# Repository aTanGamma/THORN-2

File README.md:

# aTan's THORN-2 RISC-V CPU Project

## What?

This is an implementation of the RISC-V spec using nothing but basic logic and
memory elements. 

The project has been inspired by several similar projects, most
notably [Robert Baruch's LMARV-1](https://www.youtube.com/playlist?list=PLEeZWGE3PwbansoxKjjMKHQqS_2cm8i60),
[James Sharman's JAM-1](https://www.youtube.com/playlist?list=PLFhc0MFC8MiCDOh3cGFji3qQfXziB9yOw)
and [Fabian Schuiki's Superscalar CPU](https://www.youtube.com/playlist?list=PLyR4neQXqQo5nPdEiMbaEJxWiy_UuyNN4).

As of May '26 I'm looking to implement the RV64I spec, with vague plans to 
extend this with the M and maybe F modules. I don't have any timeframe for that
though.

## Why?

IDK. It's fun :)

## That's mental... Where can I see the details?

If you go to `Docs/Writeup/` you can see a proper typewritten rundown on how
everything works and my "design process". There's quite a bit of techy stuff
there, and it's not _guaranteed_ to make sense - it's mostly a document to help
me keep track of what I'm doing between each section.

## Where are the schematics?

See `Schematics/`. This will be spotty for a while yet.

## Can I do anything with this project?

Please do! Though do read the license first. Broadly speaking, keep everything
open-source and don't be evil :)

## What happened to the THORN-1?

¬_¬ it went wrong...

In reality, it was the same as this project, but massively overcomplicated and
everything I learned there helped make this version much simpler. T1 used
pipelined ram for the registers, leading to a 4-phase clock and massive pain in
the ALU, so I abandoned it to start over.

-aTan 2026

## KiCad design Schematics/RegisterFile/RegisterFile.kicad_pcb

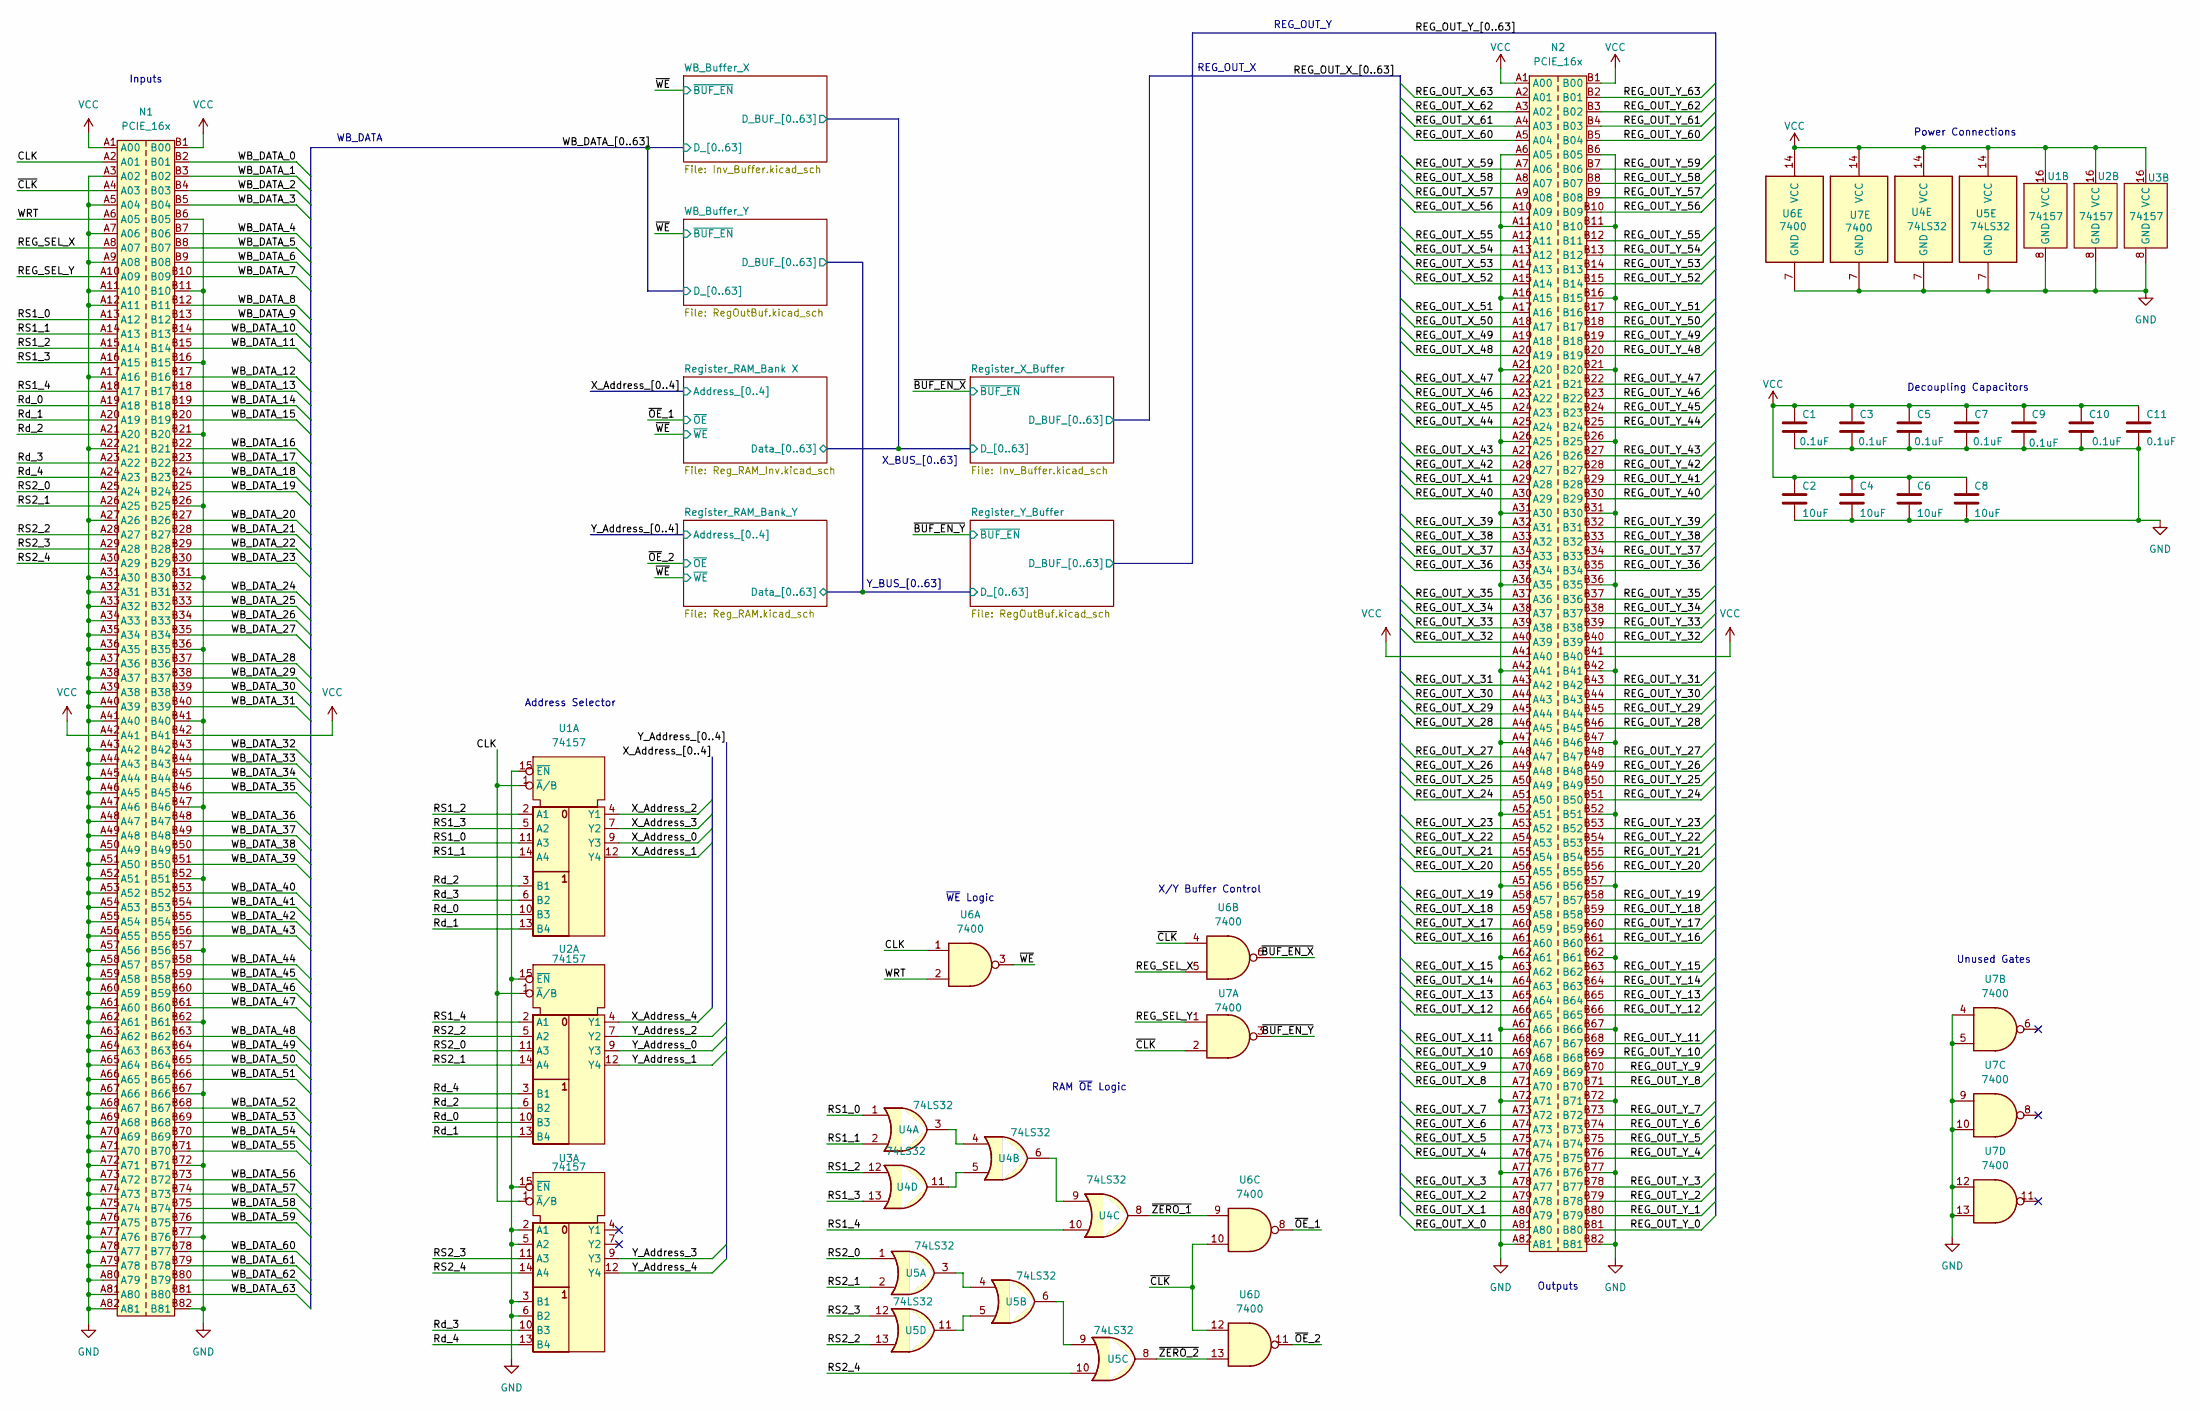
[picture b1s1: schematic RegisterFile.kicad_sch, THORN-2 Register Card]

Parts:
C1, C3, C5, C7, C9, C10, C11: 0.1uF; C_1206_3216Metric
C2, C4, C6, C8: 10uF; C_1206_3216Metric
N1, N2: PCIE_16x; BUS_PCIexpress_x16
U1, U2, U3: 74157; SOIC-16_3.9x9.9mm_P1.27mm
U4, U5: 74LS32; TSSOP-14_4.4x5mm_P0.65mm
U6, U7: 7400; TSSOP-14_4.4x5mm_P0.65mm

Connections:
/CLK: N1.A2 (A01), U1.1 (~A/B), U2.1 (~A/B), U3.1 (~A/B), U6.1
/REG_OUT_X_0: N2.A81 (A80); also elsewhere on the board
/REG_OUT_X_1: N2.A80 (A79); also elsewhere on the board
/REG_OUT_X_2: N2.A79 (A78); also elsewhere on the board
/REG_OUT_X_3: N2.A78 (A77); also elsewhere on the board
/REG_OUT_X_4: N2.A76 (A75); also elsewhere on the board
/REG_OUT_X_5: N2.A75 (A74); also elsewhere on the board
/REG_OUT_X_6: N2.A74 (A73); also elsewhere on the board
/REG_OUT_X_7: N2.A73 (A72); also elsewhere on the board
/REG_OUT_X_8: N2.A71 (A70); also elsewhere on the board
/REG_OUT_X_9: N2.A70 (A69); also elsewhere on the board
/REG_OUT_X_10: N2.A69 (A68); also elsewhere on the board
/REG_OUT_X_11: N2.A68 (A67); also elsewhere on the board
/REG_OUT_X_12: N2.A66 (A65); also elsewhere on the board
/REG_OUT_X_13: N2.A65 (A64); also elsewhere on the board
/REG_OUT_X_14: N2.A64 (A63); also elsewhere on the board
/REG_OUT_X_15: N2.A63 (A62); also elsewhere on the board
/REG_OUT_X_16: N2.A61 (A60); also elsewhere on the board
/REG_OUT_X_17: N2.A60 (A59); also elsewhere on the board
/REG_OUT_X_18: N2.A59 (A58); also elsewhere on the board
/REG_OUT_X_19: N2.A58 (A57); also elsewhere on the board
/REG_OUT_X_20: N2.A56 (A55); also elsewhere on the board
/REG_OUT_X_21: N2.A55 (A54); also elsewhere on the board
/REG_OUT_X_22: N2.A54 (A53); also elsewhere on the board
/REG_OUT_X_23: N2.A53 (A52); also elsewhere on the board
/REG_OUT_X_24: N2.A51 (A50); also elsewhere on the board
/REG_OUT_X_25: N2.A50 (A49); also elsewhere on the board
/REG_OUT_X_26: N2.A49 (A48); also elsewhere on the board
/REG_OUT_X_27: N2.A48 (A47); also elsewhere on the board
/REG_OUT_X_28: N2.A46 (A45); also elsewhere on the board
/REG_OUT_X_29: N2.A45 (A44); also elsewhere on the board
/REG_OUT_X_30: N2.A44 (A43); also elsewhere on the board
/REG_OUT_X_31: N2.A43 (A42); also elsewhere on the board
/REG_OUT_X_32: N2.A40 (A39); also elsewhere on the board
/REG_OUT_X_33: N2.A39 (A38); also elsewhere on the board
/REG_OUT_X_34: N2.A38 (A37); also elsewhere on the board
/REG_OUT_X_35: N2.A37 (A36); also elsewhere on the board
/REG_OUT_X_36: N2.A35 (A34); also elsewhere on the board
/REG_OUT_X_37: N2.A34 (A33); also elsewhere on the board
/REG_OUT_X_38: N2.A33 (A32); also elsewhere on the board
/REG_OUT_X_39: N2.A32 (A31); also elsewhere on the board
/REG_OUT_X_40: N2.A30 (A29); also elsewhere on the board
/REG_OUT_X_41: N2.A29 (A28); also elsewhere on the board
/REG_OUT_X_42: N2.A28 (A27); also elsewhere on the board
/REG_OUT_X_43: N2.A27 (A26); also elsewhere on the board
/REG_OUT_X_44: N2.A25 (A24); also elsewhere on the board
/REG_OUT_X_45: N2.A24 (A23); also elsewhere on the board
/REG_OUT_X_46: N2.A23 (A22); also elsewhere on the board
/REG_OUT_X_47: N2.A22 (A21); also elsewhere on the board
/REG_OUT_X_48: N2.A20 (A19); also elsewhere on the board
/REG_OUT_X_49: N2.A19 (A18); also elsewhere on the board
/REG_OUT_X_50: N2.A18 (A17); also elsewhere on the board
/REG_OUT_X_51: N2.A17 (A16); also elsewhere on the board
/REG_OUT_X_52: N2.A15 (A14); also elsewhere on the board
/REG_OUT_X_53: N2.A14 (A13); also elsewhere on the board
/REG_OUT_X_54: N2.A13 (A12); also elsewhere on the board
/REG_OUT_X_55: N2.A12 (A11); also elsewhere on the board
/REG_OUT_X_56: N2.A10 (A09); also elsewhere on the board
/REG_OUT_X_57: N2.A9 (A08); also elsewhere on the board
/REG_OUT_X_58: N2.A8 (A07); also elsewhere on the board
/REG_OUT_X_59: N2.A7 (A06); also elsewhere on the board
/REG_OUT_X_60: N2.A5 (A04); also elsewhere on the board
/REG_OUT_X_61: N2.A4 (A03); also elsewhere on the board
/REG_OUT_X_62: N2.A3 (A02); also elsewhere on the board
/REG_OUT_X_63: N2.A2 (A01); also elsewhere on the board
/REG_OUT_Y_0: N2.B81 (B80); also elsewhere on the board
/REG_OUT_Y_1: N2.B80 (B79); also elsewhere on the board
/REG_OUT_Y_2: N2.B79 (B78); also elsewhere on the board
/REG_OUT_Y_3: N2.B78 (B77); also elsewhere on the board
/REG_OUT_Y_4: N2.B76 (B75); also elsewhere on the board
/REG_OUT_Y_5: N2.B75 (B74); also elsewhere on the board
/REG_OUT_Y_6: N2.B74 (B73); also elsewhere on the board
/REG_OUT_Y_7: N2.B73 (B72); also elsewhere on the board
/REG_OUT_Y_8: N2.B71 (B70); also elsewhere on the board
/REG_OUT_Y_9: N2.B70 (B69); also elsewhere on the board
/REG_OUT_Y_10: N2.B69 (B68); also elsewhere on the board
/REG_OUT_Y_11: N2.B68 (B67); also elsewhere on the board
/REG_OUT_Y_12: N2.B66 (B65); also elsewhere on the board
/REG_OUT_Y_13: N2.B65 (B64); also elsewhere on the board
/REG_OUT_Y_14: N2.B64 (B63); also elsewhere on the board
/REG_OUT_Y_15: N2.B63 (B62); also elsewhere on the board
/REG_OUT_Y_16: N2.B61 (B60); also elsewhere on the board
/REG_OUT_Y_17: N2.B60 (B59); also elsewhere on the board
/REG_OUT_Y_18: N2.B59 (B58); also elsewhere on the board
/REG_OUT_Y_19: N2.B58 (B57); also elsewhere on the board
/REG_OUT_Y_20: N2.B56 (B55); also elsewhere on the board
/REG_OUT_Y_21: N2.B55 (B54); also elsewhere on the board
/REG_OUT_Y_22: N2.B54 (B53); also elsewhere on the board
/REG_OUT_Y_23: N2.B53 (B52); also elsewhere on the board
/REG_OUT_Y_24: N2.B51 (B50); also elsewhere on the board
/REG_OUT_Y_25: N2.B50 (B49); also elsewhere on the board
/REG_OUT_Y_26: N2.B49 (B48); also elsewhere on the board
/REG_OUT_Y_27: N2.B48 (B47); also elsewhere on the board
/REG_OUT_Y_28: N2.B46 (B45); also elsewhere on the board
/REG_OUT_Y_29: N2.B45 (B44); also elsewhere on the board
/REG_OUT_Y_30: N2.B44 (B43); also elsewhere on the board
/REG_OUT_Y_31: N2.B43 (B42); also elsewhere on the board
/REG_OUT_Y_32: N2.B40 (B39); also elsewhere on the board
/REG_OUT_Y_33: N2.B39 (B38); also elsewhere on the board
/REG_OUT_Y_34: N2.B38 (B37); also elsewhere on the board
/REG_OUT_Y_35: N2.B37 (B36); also elsewhere on the board
/REG_OUT_Y_36: N2.B35 (B34); also elsewhere on the board
/REG_OUT_Y_37: N2.B34 (B33); also elsewhere on the board
/REG_OUT_Y_38: N2.B33 (B32); also elsewhere on the board
/REG_OUT_Y_39: N2.B32 (B31); also elsewhere on the board
/REG_OUT_Y_40: N2.B30 (B29); also elsewhere on the board
/REG_OUT_Y_41: N2.B29 (B28); also elsewhere on the board
/REG_OUT_Y_42: N2.B28 (B27); also elsewhere on the board
/REG_OUT_Y_43: N2.B27 (B26); also elsewhere on the board
/REG_OUT_Y_44: N2.B25 (B24); also elsewhere on the board
/REG_OUT_Y_45: N2.B24 (B23); also elsewhere on the board
/REG_OUT_Y_46: N2.B23 (B22); also elsewhere on the board
/REG_OUT_Y_47: N2.B22 (B21); also elsewhere on the board
/REG_OUT_Y_48: N2.B20 (B19); also elsewhere on the board
/REG_OUT_Y_49: N2.B19 (B18); also elsewhere on the board
/REG_OUT_Y_50: N2.B18 (B17); also elsewhere on the board
/REG_OUT_Y_51: N2.B17 (B16); also elsewhere on the board
/REG_OUT_Y_52: N2.B15 (B14); also elsewhere on the board
/REG_OUT_Y_53: N2.B14 (B13); also elsewhere on the board
/REG_OUT_Y_54: N2.B13 (B12); also elsewhere on the board
/REG_OUT_Y_55: N2.B12 (B11); also elsewhere on the board
/REG_OUT_Y_56: N2.B10 (B09); also elsewhere on the board
/REG_OUT_Y_57: N2.B9 (B08); also elsewhere on the board
/REG_OUT_Y_58: N2.B8 (B07); also elsewhere on the board
/REG_OUT_Y_59: N2.B7 (B06); also elsewhere on the board
/REG_OUT_Y_60: N2.B5 (B04); also elsewhere on the board
/REG_OUT_Y_61: N2.B4 (B03); also elsewhere on the board
/REG_OUT_Y_62: N2.B3 (B02); also elsewhere on the board
/REG_OUT_Y_63: N2.B2 (B01); also elsewhere on the board
/REG_SEL_X: N1.A8 (A07), U6.5
/REG_SEL_Y: N1.A10 (A09), U7.1
/RS1_0: N1.A13 (A12), U1.11 (A3), U4.1
/RS1_1: N1.A14 (A13), U1.14 (A4), U4.2
/RS1_2: N1.A15 (A14), U1.2 (A1), U4.12
/RS1_3: N1.A16 (A15), U1.5 (A2), U4.13
/RS1_4: N1.A18 (A17), U2.2 (A1), U4.10
/RS2_0: N1.A25 (A24), U2.11 (A3), U5.1
/RS2_1: N1.A26 (A25), U2.14 (A4), U5.2
/RS2_2: N1.A28 (A27), U2.5 (A2), U5.13
/RS2_3: N1.A29 (A28), U3.11 (A3), U5.12
/RS2_4: N1.A30 (A29), U3.14 (A4), U5.10
/Rd_0: N1.A19 (A18), U1.10 (B3), U2.10 (B3)
/Rd_1: N1.A20 (A19), U1.13 (B4), U2.13 (B4)
/Rd_2: N1.A21 (A20), U1.3 (B1), U2.6 (B2)
/Rd_3: N1.A23 (A22), U1.6 (B2), U3.10 (B3)
/Rd_4: N1.A24 (A23), U2.3 (B1), U3.13 (B4)
/WB_DATA_0: N1.B2 (B01); also elsewhere on the board
/WB_DATA_1: N1.B3 (B02); also elsewhere on the board
/WB_DATA_2: N1.B4 (B03); also elsewhere on the board
/WB_DATA_3: N1.B5 (B04); also elsewhere on the board
/WB_DATA_4: N1.B7 (B06); also elsewhere on the board
/WB_DATA_5: N1.B8 (B07); also elsewhere on the board
/WB_DATA_6: N1.B9 (B08); also elsewhere on the board
/WB_DATA_7: N1.B10 (B09); also elsewhere on the board
/WB_DATA_8: N1.B12 (B11); also elsewhere on the board
/WB_DATA_9: N1.B13 (B12); also elsewhere on the board
/WB_DATA_10: N1.B14 (B13); also elsewhere on the board
/WB_DATA_11: N1.B15 (B14); also elsewhere on the board
/WB_DATA_12: N1.B17 (B16); also elsewhere on the board
/WB_DATA_13: N1.B18 (B17); also elsewhere on the board
/WB_DATA_14: N1.B19 (B18); also elsewhere on the board
/WB_DATA_15: N1.B20 (B19); also elsewhere on the board
/WB_DATA_16: N1.B22 (B21); also elsewhere on the board
/WB_DATA_17: N1.B23 (B22); also elsewhere on the board
/WB_DATA_18: N1.B24 (B23); also elsewhere on the board
/WB_DATA_19: N1.B25 (B24); also elsewhere on the board
/WB_DATA_20: N1.B27 (B26); also elsewhere on the board
/WB_DATA_21: N1.B28 (B27); also elsewhere on the board
/WB_DATA_22: N1.B29 (B28); also elsewhere on the board
/WB_DATA_23: N1.B30 (B29); also elsewhere on the board
/WB_DATA_24: N1.B32 (B31); also elsewhere on the board
/WB_DATA_25: N1.B33 (B32); also elsewhere on the board
/WB_DATA_26: N1.B34 (B33); also elsewhere on the board
/WB_DATA_27: N1.B35 (B34); also elsewhere on the board
/WB_DATA_28: N1.B37 (B36); also elsewhere on the board
/WB_DATA_29: N1.B38 (B37); also elsewhere on the board
/WB_DATA_30: N1.B39 (B38); also elsewhere on the board
/WB_DATA_31: N1.B40 (B39); also elsewhere on the board
/WB_DATA_32: N1.B43 (B42); also elsewhere on the board
/WB_DATA_33: N1.B44 (B43); also elsewhere on the board
/WB_DATA_34: N1.B45 (B44); also elsewhere on the board
/WB_DATA_35: N1.B46 (B45); also elsewhere on the board
/WB_DATA_36: N1.B48 (B47); also elsewhere on the board
/WB_DATA_37: N1.B49 (B48); also elsewhere on the board
/WB_DATA_38: N1.B50 (B49); also elsewhere on the board
/WB_DATA_39: N1.B51 (B50); also elsewhere on the board
/WB_DATA_40: N1.B53 (B52); also elsewhere on the board
/WB_DATA_41: N1.B54 (B53); also elsewhere on the board
/WB_DATA_42: N1.B55 (B54); also elsewhere on the board
/WB_DATA_43: N1.B56 (B55); also elsewhere on the board
/WB_DATA_44: N1.B58 (B57); also elsewhere on the board
/WB_DATA_45: N1.B59 (B58); also elsewhere on the board
/WB_DATA_46: N1.B60 (B59); also elsewhere on the board
/WB_DATA_47: N1.B61 (B60); also elsewhere on the board
/WB_DATA_48: N1.B63 (B62); also elsewhere on the board
/WB_DATA_49: N1.B64 (B63); also elsewhere on the board
/WB_DATA_50: N1.B65 (B64); also elsewhere on the board
/WB_DATA_51: N1.B66 (B65); also elsewhere on the board
/WB_DATA_52: N1.B68 (B67); also elsewhere on the board
/WB_DATA_53: N1.B69 (B68); also elsewhere on the board
/WB_DATA_54: N1.B70 (B69); also elsewhere on the board
/WB_DATA_55: N1.B71 (B70); also elsewhere on the board
/WB_DATA_56: N1.B73 (B72); also elsewhere on the board
/WB_DATA_57: N1.B74 (B73); also elsewhere on the board
/WB_DATA_58: N1.B75 (B74); also elsewhere on the board
/WB_DATA_59: N1.B76 (B75); also elsewhere on the board
/WB_DATA_60: N1.B78 (B77); also elsewhere on the board
/WB_DATA_61: N1.B79 (B78); also elsewhere on the board
/WB_DATA_62: N1.B80 (B79); also elsewhere on the board
/WB_DATA_63: N1.B81 (B80); also elsewhere on the board
/WRT: N1.A6 (A05), U6.2
/X_Address_0: U1.9 (Y3); also elsewhere on the board
/X_Address_1: U1.12 (Y4); also elsewhere on the board
/X_Address_2: U1.4 (Y1); also elsewhere on the board
/X_Address_3: U1.7 (Y2); also elsewhere on the board
/X_Address_4: U2.4 (Y1); also elsewhere on the board
/Y_Address_0: U2.9 (Y3); also elsewhere on the board
/Y_Address_1: U2.12 (Y4); also elsewhere on the board
/Y_Address_2: U2.7 (Y2); also elsewhere on the board
/Y_Address_3: U3.9 (Y3); also elsewhere on the board
/Y_Address_4: U3.12 (Y4); also elsewhere on the board
/~BUF_EN_X: U6.6; also elsewhere on the board
/~BUF_EN_Y: U7.3; also elsewhere on the board
/~CLK: N1.A4 (A03), U6.4, U6.10, U6.12, U7.2
/~OE_1: U6.8; also elsewhere on the board
/~OE_2: U6.11; also elsewhere on the board
/~WE: U6.3; also elsewhere on the board
/~ZERO_1: U4.8, U6.9
/~ZERO_2: U5.8, U6.13
GND: C1.2, C2.2, C3.2, C4.2, C5.2, C6.2, C7.2, C8.2, C9.2, C10.2, C11.2, N1.A3 (A02), N1.A5 (A04), N1.A7 (A06), N1.A9 (A08), N1.A11 (A10), N1.A12 (A11), N1.A17 (A16), N1.A22 (A21), N1.A27 (A26), N1.A31 (A30), N1.A32 (A31), N1.A33 (A32), N1.A34 (A33), N1.A35 (A34), N1.A36 (A35), N1.A37 (A36), N1.A38 (A37), N1.A39 (A38), N1.A40 (A39), N1.A41 (A40), N1.A43 (A42), N1.A44 (A43), N1.A45 (A44), N1.A46 (A45), N1.A47 (A46), N1.A48 (A47), N1.A49 (A48), N1.A50 (A49), N1.A51 (A50), N1.A52 (A51), N1.A53 (A52), N1.A54 (A53), N1.A55 (A54), N1.A56 (A55), N1.A57 (A56), N1.A58 (A57), N1.A59 (A58), N1.A60 (A59), N1.A61 (A60), N1.A62 (A61), N1.A63 (A62), N1.A64 (A63), N1.A65 (A64), N1.A66 (A65), N1.A67 (A66), N1.A68 (A67), N1.A69 (A68), N1.A70 (A69), N1.A71 (A70), N1.A72 (A71), N1.A73 (A72), N1.A74 (A73), N1.A75 (A74), N1.A76 (A75), N1.A77 (A76), N1.A78 (A77), N1.A79 (A78), N1.A80 (A79), N1.A81 (A80), N1.A82 (A81), N1.B6 (B05), N1.B11 (B10), N1.B16 (B15), N1.B21 (B20), N1.B26 (B25), N1.B31 (B30), N1.B36 (B35), N1.B41 (B40), N1.B47 (B46), N1.B52 (B51), N1.B57 (B56), N1.B62 (B61), N1.B67 (B66), N1.B72 (B71), N1.B77 (B76), N1.B82 (B81), N2.A6 (A05), N2.A11 (A10), N2.A16 (A15), N2.A21 (A20), N2.A26 (A25), N2.A31 (A30), N2.A36 (A35), N2.A42 (A41), N2.A47 (A46), N2.A52 (A51), N2.A57 (A56), N2.A62 (A61), N2.A67 (A66), N2.A72 (A71), N2.A77 (A76), N2.A82 (A81), N2.B6 (B05), N2.B11 (B10), N2.B16 (B15), N2.B21 (B20), N2.B26 (B25), N2.B31 (B30), N2.B36 (B35), N2.B42 (B41), N2.B47 (B46), N2.B52 (B51), N2.B57 (B56), N2.B62 (B61), N2.B67 (B66), N2.B72 (B71), N2.B77 (B76), N2.B82 (B81), U1.8 (GND), U1.15 (~EN), U2.8 (GND), U2.15 (~EN), U3.2 (A1), U3.3 (B1), U3.5 (A2), U3.6 (B2), U3.8 (GND), U3.15 (~EN), U4.7 (GND), U5.7 (GND), U6.7 (GND), U7.4, U7.5, U7.7 (GND), U7.9, U7.10, U7.12, U7.13; also elsewhere on the board
unnamed: U4.3, U4.4
unnamed: U4.6, U4.9
unnamed: U4.5, U4.11
unnamed: U5.3, U5.4
unnamed: U5.6, U5.9
unnamed: U5.5, U5.11
VCC: C1.1, C2.1, C3.1, C4.1, C5.1, C6.1, C7.1, C8.1, C9.1, C10.1, C11.1, N1.A1 (A00), N1.A42 (A41), N1.B1 (B00), N1.B42 (B41), N2.A1 (A00), N2.A41 (A40), N2.B1 (B00), N2.B41 (B40), U1.16 (VCC), U2.16 (VCC), U3.16 (VCC), U4.14 (VCC), U5.14 (VCC), U6.14 (VCC), U7.14 (VCC); also elsewhere on the board

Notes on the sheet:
RAM ~{OE} Logic
Power Connections
Y_BUS_[0..63]
X_BUS_[0..63]
Unused Gates
Decoupling Capacitors
REG_OUT_X
REG_OUT_Y
~{WE} Logic
Outputs
WB_DATA
Address Selector
Inputs
X/Y Buffer Control

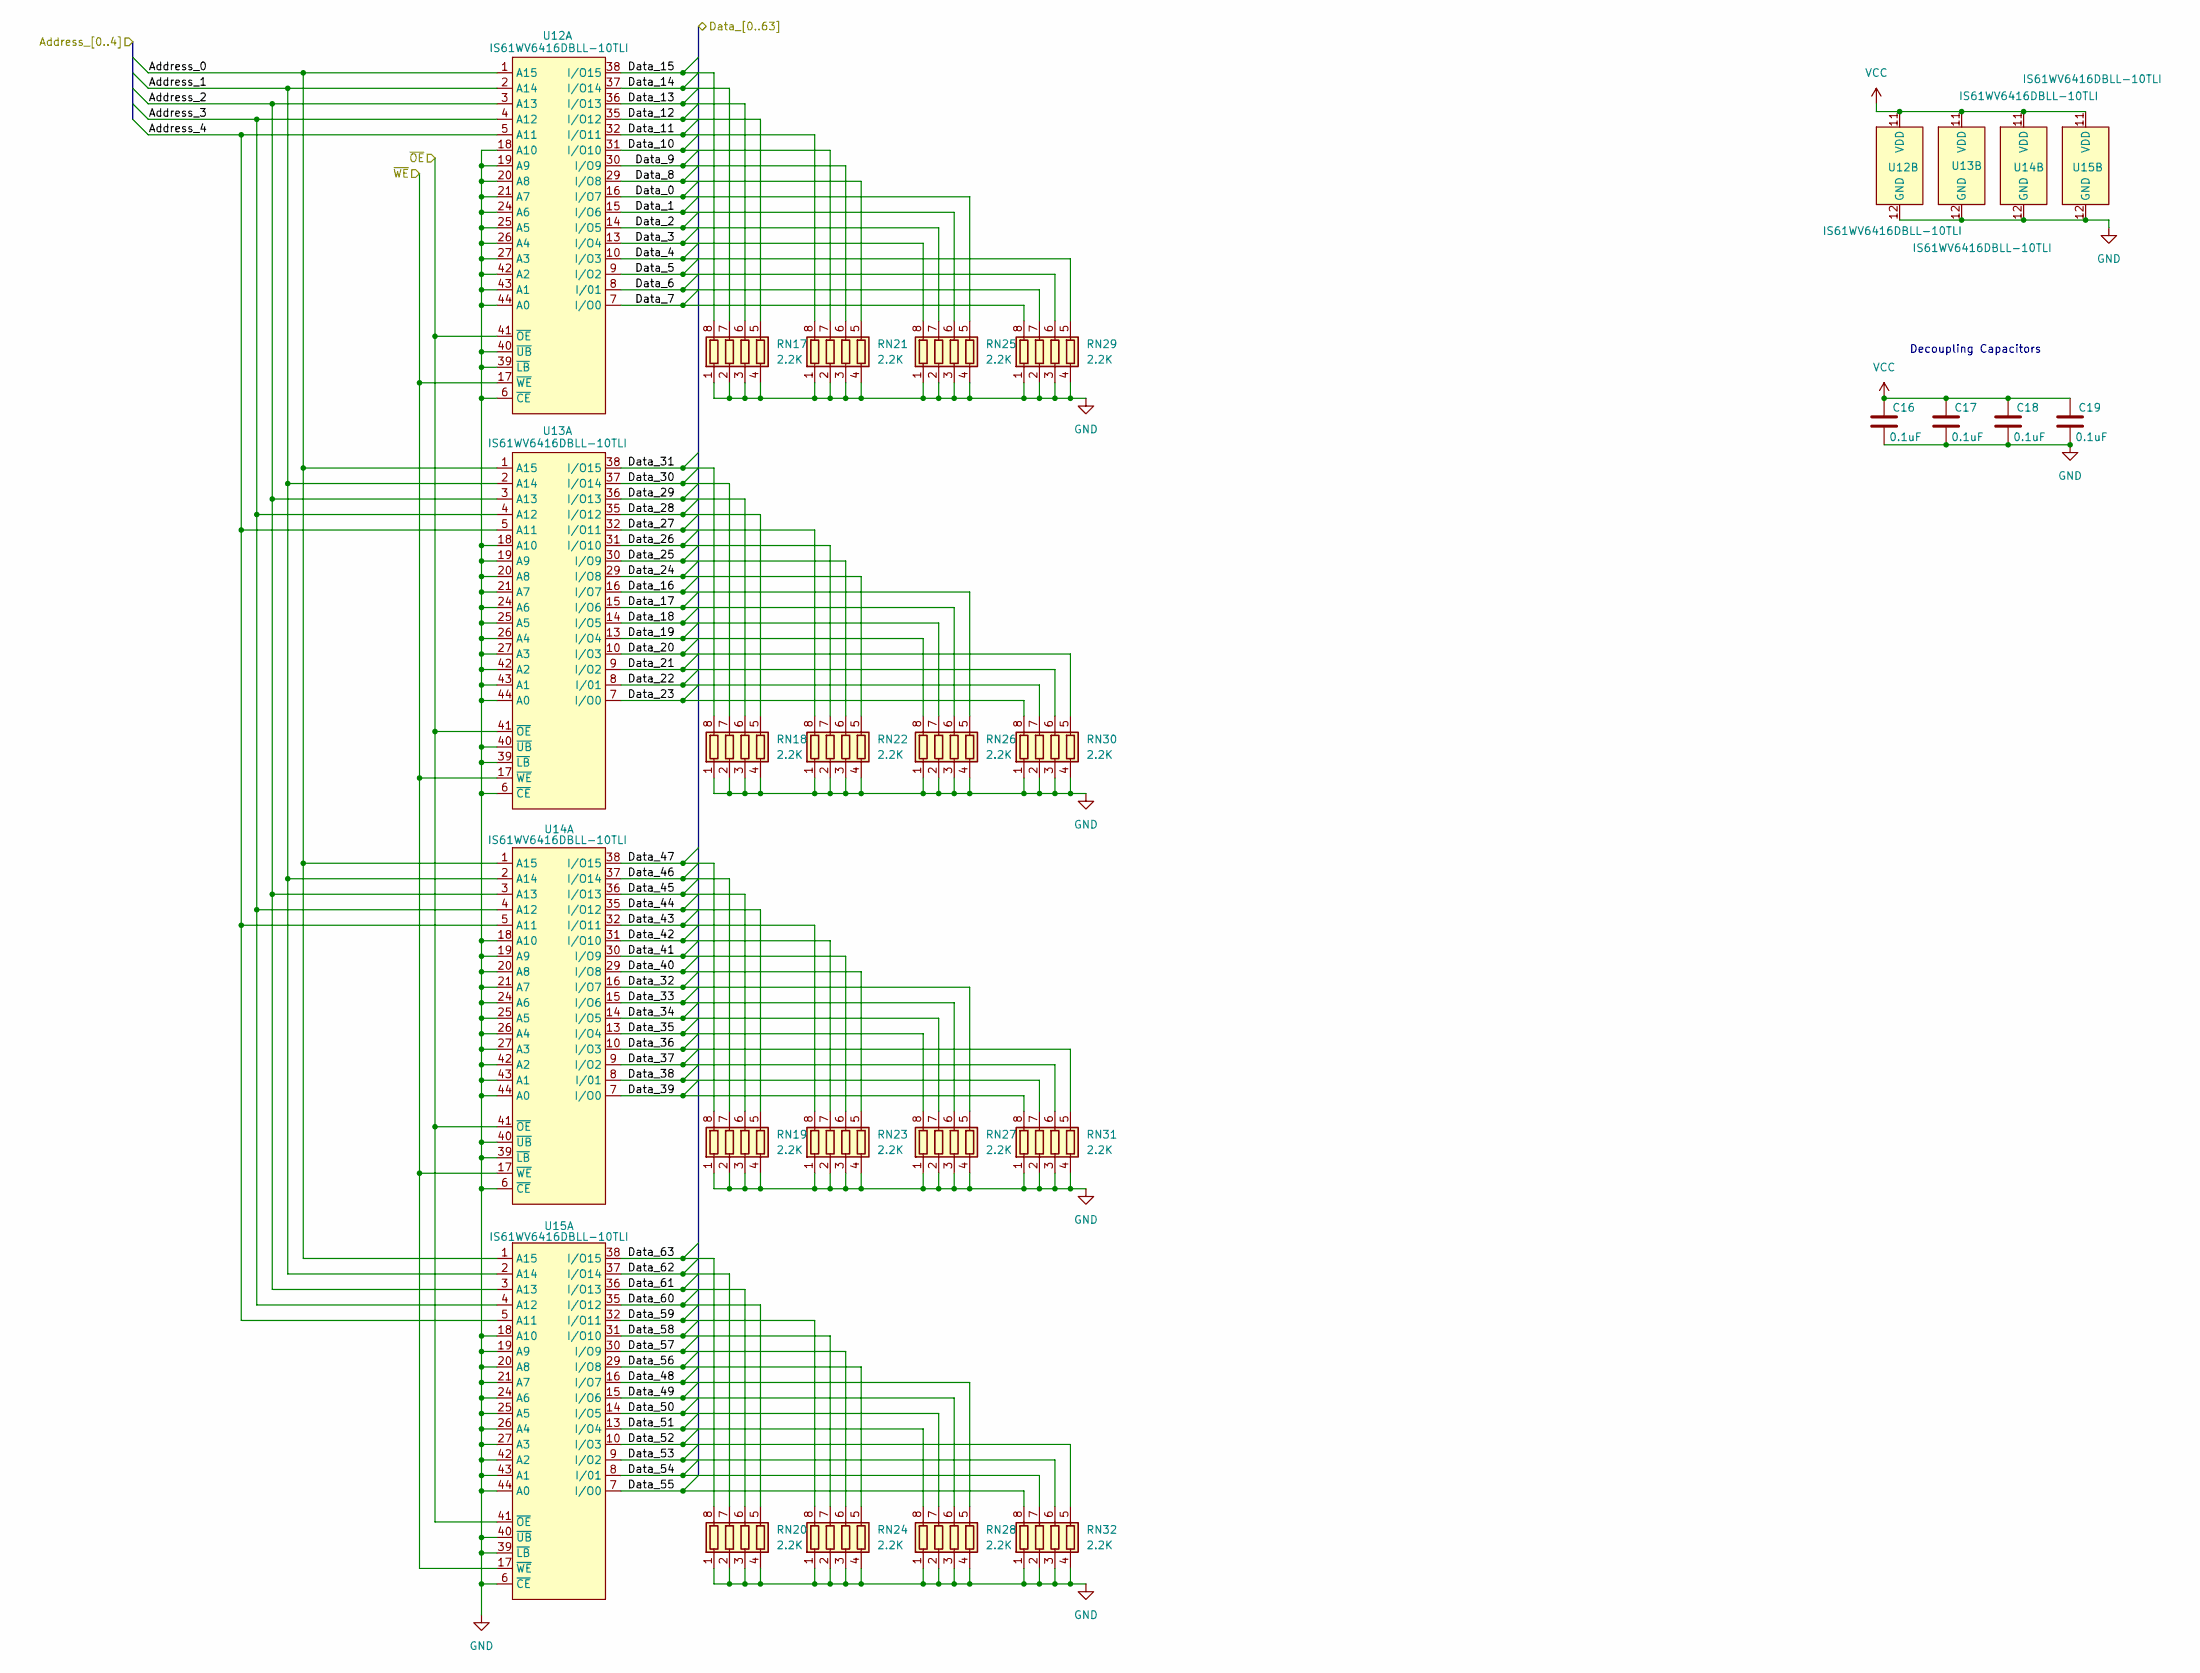
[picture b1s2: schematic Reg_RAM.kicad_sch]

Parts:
C16, C17, C18, C19: 0.1uF; C_1206_3216Metric
RN17, RN18, RN19, RN20, RN21, RN22, RN23, RN24, RN25, RN26, RN27, RN28, RN29, RN30, RN31, RN32: 2.2K; R_Array_Convex_4x0603
U12, U13, U14, U15: IS61WV6416DBLL-10TLI; TSOP-II-44_10.16x18.41mm_P0.8mm

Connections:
/Register_RAM_Bank_Y/Data_0: RN25.5 (R4.2), U12.16 (I/O7); also elsewhere on the board
/Register_RAM_Bank_Y/Data_1: RN25.6 (R3.2), U12.15 (I/O6); also elsewhere on the board
/Register_RAM_Bank_Y/Data_2: RN25.7 (R2.2), U12.14 (I/O5); also elsewhere on the board
/Register_RAM_Bank_Y/Data_3: RN25.8 (R1.2), U12.13 (I/O4); also elsewhere on the board
/Register_RAM_Bank_Y/Data_4: RN29.5 (R4.2), U12.10 (I/O3); also elsewhere on the board
/Register_RAM_Bank_Y/Data_5: RN29.6 (R3.2), U12.9 (I/O2); also elsewhere on the board
/Register_RAM_Bank_Y/Data_6: RN29.7 (R2.2), U12.8 (I/01); also elsewhere on the board
/Register_RAM_Bank_Y/Data_7: RN29.8 (R1.2), U12.7 (I/O0); also elsewhere on the board
/Register_RAM_Bank_Y/Data_8: RN21.5 (R4.2), U12.29 (I/O8); also elsewhere on the board
/Register_RAM_Bank_Y/Data_9: RN21.6 (R3.2), U12.30 (I/O9); also elsewhere on the board
/Register_RAM_Bank_Y/Data_10: RN21.7 (R2.2), U12.31 (I/O10); also elsewhere on the board
/Register_RAM_Bank_Y/Data_11: RN21.8 (R1.2), U12.32 (I/O11); also elsewhere on the board
/Register_RAM_Bank_Y/Data_12: RN17.5 (R4.2), U12.35 (I/O12); also elsewhere on the board
/Register_RAM_Bank_Y/Data_13: RN17.6 (R3.2), U12.36 (I/O13); also elsewhere on the board
/Register_RAM_Bank_Y/Data_14: RN17.7 (R2.2), U12.37 (I/O14); also elsewhere on the board
/Register_RAM_Bank_Y/Data_15: RN17.8 (R1.2), U12.38 (I/O15); also elsewhere on the board
/Register_RAM_Bank_Y/Data_16: RN26.5 (R4.2), U13.16 (I/O7); also elsewhere on the board
/Register_RAM_Bank_Y/Data_17: RN26.6 (R3.2), U13.15 (I/O6); also elsewhere on the board
/Register_RAM_Bank_Y/Data_18: RN26.7 (R2.2), U13.14 (I/O5); also elsewhere on the board
/Register_RAM_Bank_Y/Data_19: RN26.8 (R1.2), U13.13 (I/O4); also elsewhere on the board
/Register_RAM_Bank_Y/Data_20: RN30.5 (R4.2), U13.10 (I/O3); also elsewhere on the board
/Register_RAM_Bank_Y/Data_21: RN30.6 (R3.2), U13.9 (I/O2); also elsewhere on the board
/Register_RAM_Bank_Y/Data_22: RN30.7 (R2.2), U13.8 (I/01); also elsewhere on the board
/Register_RAM_Bank_Y/Data_23: RN30.8 (R1.2), U13.7 (I/O0); also elsewhere on the board
/Register_RAM_Bank_Y/Data_24: RN22.5 (R4.2), U13.29 (I/O8); also elsewhere on the board
/Register_RAM_Bank_Y/Data_25: RN22.6 (R3.2), U13.30 (I/O9); also elsewhere on the board
/Register_RAM_Bank_Y/Data_26: RN22.7 (R2.2), U13.31 (I/O10); also elsewhere on the board
/Register_RAM_Bank_Y/Data_27: RN22.8 (R1.2), U13.32 (I/O11); also elsewhere on the board
/Register_RAM_Bank_Y/Data_28: RN18.5 (R4.2), U13.35 (I/O12); also elsewhere on the board
/Register_RAM_Bank_Y/Data_29: RN18.6 (R3.2), U13.36 (I/O13); also elsewhere on the board
/Register_RAM_Bank_Y/Data_30: RN18.7 (R2.2), U13.37 (I/O14); also elsewhere on the board
/Register_RAM_Bank_Y/Data_31: RN18.8 (R1.2), U13.38 (I/O15); also elsewhere on the board
/Register_RAM_Bank_Y/Data_32: RN27.5 (R4.2), U14.16 (I/O7); also elsewhere on the board
/Register_RAM_Bank_Y/Data_33: RN27.6 (R3.2), U14.15 (I/O6); also elsewhere on the board
/Register_RAM_Bank_Y/Data_34: RN27.7 (R2.2), U14.14 (I/O5); also elsewhere on the board
/Register_RAM_Bank_Y/Data_35: RN27.8 (R1.2), U14.13 (I/O4); also elsewhere on the board
/Register_RAM_Bank_Y/Data_36: RN31.5 (R4.2), U14.10 (I/O3); also elsewhere on the board
/Register_RAM_Bank_Y/Data_37: RN31.6 (R3.2), U14.9 (I/O2); also elsewhere on the board
/Register_RAM_Bank_Y/Data_38: RN31.7 (R2.2), U14.8 (I/01); also elsewhere on the board
/Register_RAM_Bank_Y/Data_39: RN31.8 (R1.2), U14.7 (I/O0); also elsewhere on the board
/Register_RAM_Bank_Y/Data_40: RN23.5 (R4.2), U14.29 (I/O8); also elsewhere on the board
/Register_RAM_Bank_Y/Data_41: RN23.6 (R3.2), U14.30 (I/O9); also elsewhere on the board
/Register_RAM_Bank_Y/Data_42: RN23.7 (R2.2), U14.31 (I/O10); also elsewhere on the board
/Register_RAM_Bank_Y/Data_43: RN23.8 (R1.2), U14.32 (I/O11); also elsewhere on the board
/Register_RAM_Bank_Y/Data_44: RN19.5 (R4.2), U14.35 (I/O12); also elsewhere on the board
/Register_RAM_Bank_Y/Data_45: RN19.6 (R3.2), U14.36 (I/O13); also elsewhere on the board
/Register_RAM_Bank_Y/Data_46: RN19.7 (R2.2), U14.37 (I/O14); also elsewhere on the board
/Register_RAM_Bank_Y/Data_47: RN19.8 (R1.2), U14.38 (I/O15); also elsewhere on the board
/Register_RAM_Bank_Y/Data_48: RN28.5 (R4.2), U15.16 (I/O7); also elsewhere on the board
/Register_RAM_Bank_Y/Data_49: RN28.6 (R3.2), U15.15 (I/O6); also elsewhere on the board
/Register_RAM_Bank_Y/Data_50: RN28.7 (R2.2), U15.14 (I/O5); also elsewhere on the board
/Register_RAM_Bank_Y/Data_51: RN28.8 (R1.2), U15.13 (I/O4); also elsewhere on the board
/Register_RAM_Bank_Y/Data_52: RN32.5 (R4.2), U15.10 (I/O3); also elsewhere on the board
/Register_RAM_Bank_Y/Data_53: RN32.6 (R3.2), U15.9 (I/O2); also elsewhere on the board
/Register_RAM_Bank_Y/Data_54: RN32.7 (R2.2), U15.8 (I/01); also elsewhere on the board
/Register_RAM_Bank_Y/Data_55: RN32.8 (R1.2), U15.7 (I/O0); also elsewhere on the board
/Register_RAM_Bank_Y/Data_56: RN24.5 (R4.2), U15.29 (I/O8); also elsewhere on the board
/Register_RAM_Bank_Y/Data_57: RN24.6 (R3.2), U15.30 (I/O9); also elsewhere on the board
/Register_RAM_Bank_Y/Data_58: RN24.7 (R2.2), U15.31 (I/O10); also elsewhere on the board
/Register_RAM_Bank_Y/Data_59: RN24.8 (R1.2), U15.32 (I/O11); also elsewhere on the board
/Register_RAM_Bank_Y/Data_60: RN20.5 (R4.2), U15.35 (I/O12); also elsewhere on the board
/Register_RAM_Bank_Y/Data_61: RN20.6 (R3.2), U15.36 (I/O13); also elsewhere on the board
/Register_RAM_Bank_Y/Data_62: RN20.7 (R2.2), U15.37 (I/O14); also elsewhere on the board
/Register_RAM_Bank_Y/Data_63: RN20.8 (R1.2), U15.38 (I/O15); also elsewhere on the board
/Y_Address_0: U12.1 (A15), U13.1 (A15), U14.1 (A15), U15.1 (A15); also elsewhere on the board
/Y_Address_1: U12.2 (A14), U13.2 (A14), U14.2 (A14), U15.2 (A14); also elsewhere on the board
/Y_Address_2: U12.3 (A13), U13.3 (A13), U14.3 (A13), U15.3 (A13); also elsewhere on the board
/Y_Address_3: U12.4 (A12), U13.4 (A12), U14.4 (A12), U15.4 (A12); also elsewhere on the board
/Y_Address_4: U12.5 (A11), U13.5 (A11), U14.5 (A11), U15.5 (A11); also elsewhere on the board
/~OE_2: U12.41 (~OE), U13.41 (~OE), U14.41 (~OE), U15.41 (~OE); also elsewhere on the board
/~WE: U12.17 (~WE), U13.17 (~WE), U14.17 (~WE), U15.17 (~WE); also elsewhere on the board
GND: C16.2, C17.2, C18.2, C19.2, RN17.1 (R1.1), RN17.2 (R2.1), RN17.3 (R3.1), RN17.4 (R4.1), RN18.1 (R1.1), RN18.2 (R2.1), RN18.3 (R3.1), RN18.4 (R4.1), RN19.1 (R1.1), RN19.2 (R2.1), RN19.3 (R3.1), RN19.4 (R4.1), RN20.1 (R1.1), RN20.2 (R2.1), RN20.3 (R3.1), RN20.4 (R4.1), RN21.1 (R1.1), RN21.2 (R2.1), RN21.3 (R3.1), RN21.4 (R4.1), RN22.1 (R1.1), RN22.2 (R2.1), RN22.3 (R3.1), RN22.4 (R4.1), RN23.1 (R1.1), RN23.2 (R2.1), RN23.3 (R3.1), RN23.4 (R4.1), RN24.1 (R1.1), RN24.2 (R2.1), RN24.3 (R3.1), RN24.4 (R4.1), RN25.1 (R1.1), RN25.2 (R2.1), RN25.3 (R3.1), RN25.4 (R4.1), RN26.1 (R1.1), RN26.2 (R2.1), RN26.3 (R3.1), RN26.4 (R4.1), RN27.1 (R1.1), RN27.2 (R2.1), RN27.3 (R3.1), RN27.4 (R4.1), RN28.1 (R1.1), RN28.2 (R2.1), RN28.3 (R3.1), RN28.4 (R4.1), RN29.1 (R1.1), RN29.2 (R2.1), RN29.3 (R3.1), RN29.4 (R4.1), RN30.1 (R1.1), RN30.2 (R2.1), RN30.3 (R3.1), RN30.4 (R4.1), RN31.1 (R1.1), RN31.2 (R2.1), RN31.3 (R3.1), RN31.4 (R4.1), RN32.1 (R1.1), RN32.2 (R2.1), RN32.3 (R3.1), RN32.4 (R4.1), U12.6 (~CE), U12.12 (GND), U12.18 (A10), U12.19 (A9), U12.20 (A8), U12.21 (A7), U12.24 (A6), U12.25 (A5), U12.26 (A4), U12.27 (A3), U12.34 (GND), U12.39 (~LB), U12.40 (~UB), U12.42 (A2), U12.43 (A1), U12.44 (A0), U13.6 (~CE), U13.12 (GND), U13.18 (A10), U13.19 (A9), U13.20 (A8), U13.21 (A7), U13.24 (A6), U13.25 (A5), U13.26 (A4), U13.27 (A3), U13.34 (GND), U13.39 (~LB), U13.40 (~UB), U13.42 (A2), U13.43 (A1), U13.44 (A0), U14.6 (~CE), U14.12 (GND), U14.18 (A10), U14.19 (A9), U14.20 (A8), U14.21 (A7), U14.24 (A6), U14.25 (A5), U14.26 (A4), U14.27 (A3), U14.34 (GND), U14.39 (~LB), U14.40 (~UB), U14.42 (A2), U14.43 (A1), U14.44 (A0), U15.6 (~CE), U15.12 (GND), U15.18 (A10), U15.19 (A9), U15.20 (A8), U15.21 (A7), U15.24 (A6), U15.25 (A5), U15.26 (A4), U15.27 (A3), U15.34 (GND), U15.39 (~LB), U15.40 (~UB), U15.42 (A2), U15.43 (A1), U15.44 (A0); also elsewhere on the board
VCC: C16.1, C17.1, C18.1, C19.1, U12.11 (VDD), U12.33 (VDD), U13.11 (VDD), U13.33 (VDD), U14.11 (VDD), U14.33 (VDD), U15.11 (VDD), U15.33 (VDD); also elsewhere on the board

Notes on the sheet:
Decoupling Capacitors
